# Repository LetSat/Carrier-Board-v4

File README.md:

# Carrier_Board_V3
2019 Spring semester started, updated design, carrier board using the TX2i not TK1

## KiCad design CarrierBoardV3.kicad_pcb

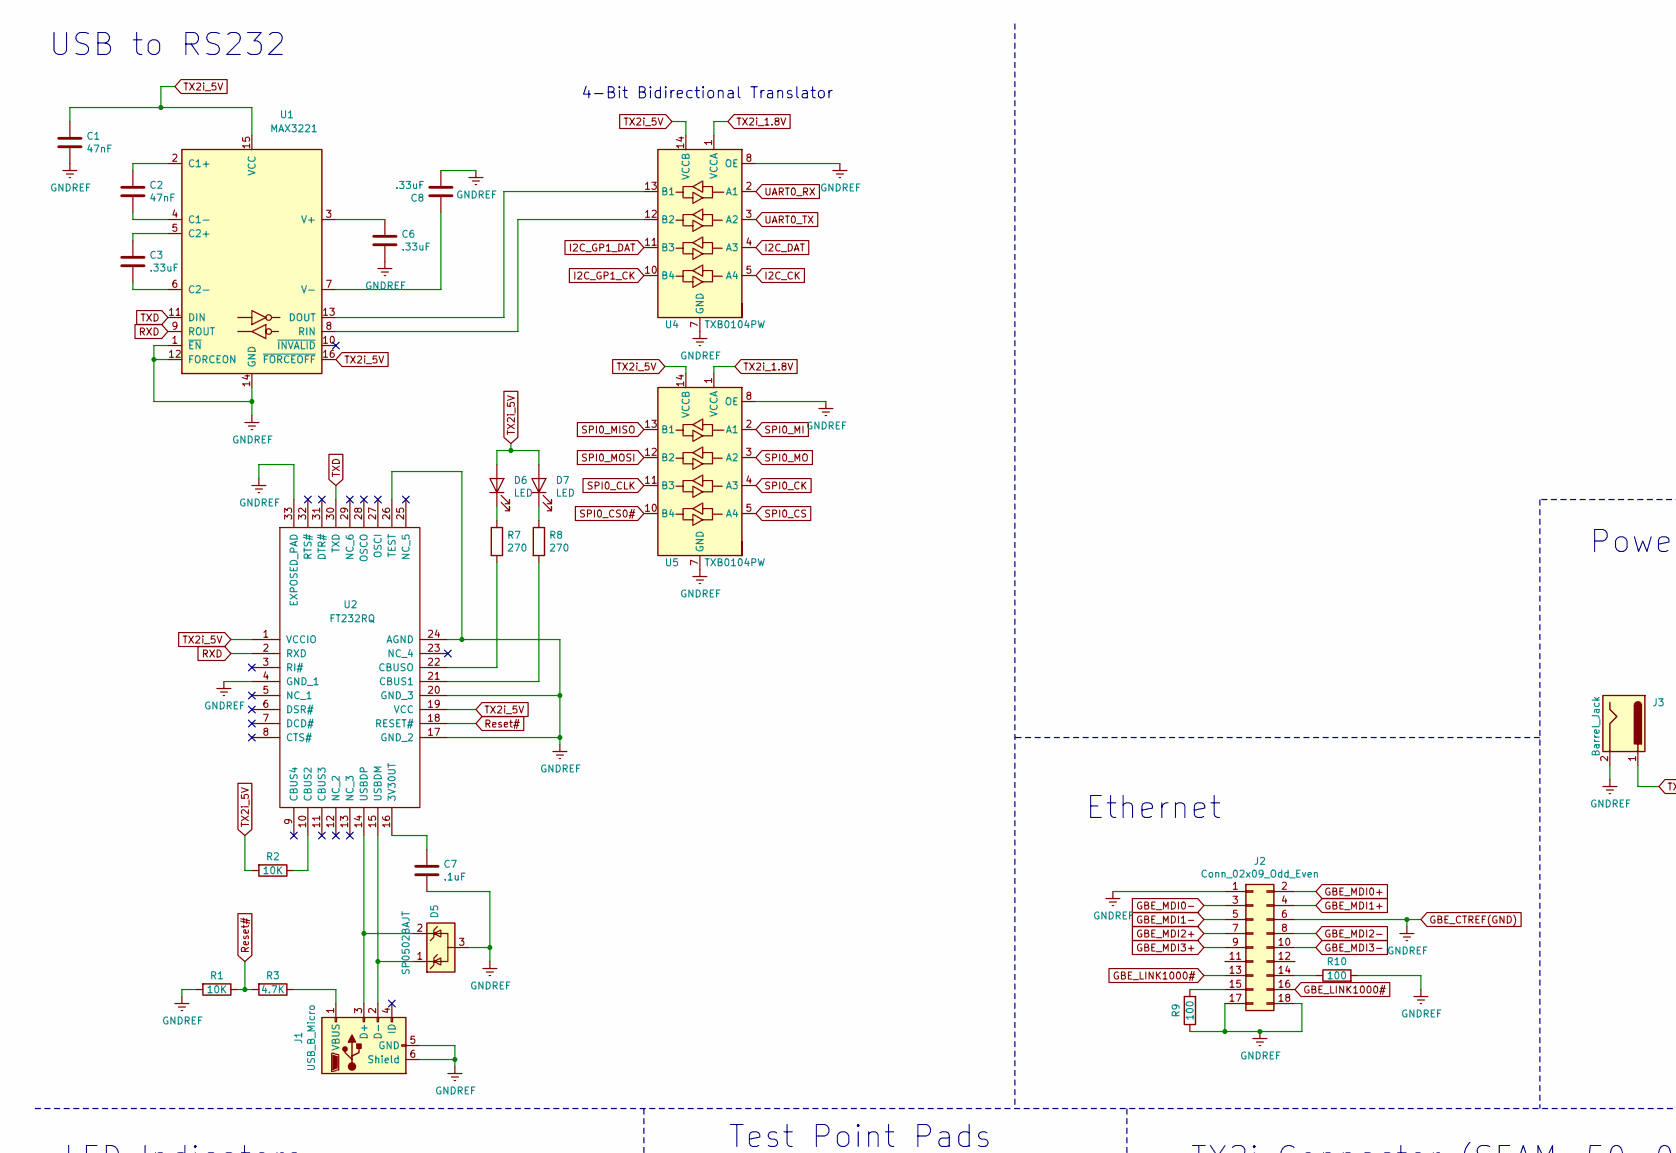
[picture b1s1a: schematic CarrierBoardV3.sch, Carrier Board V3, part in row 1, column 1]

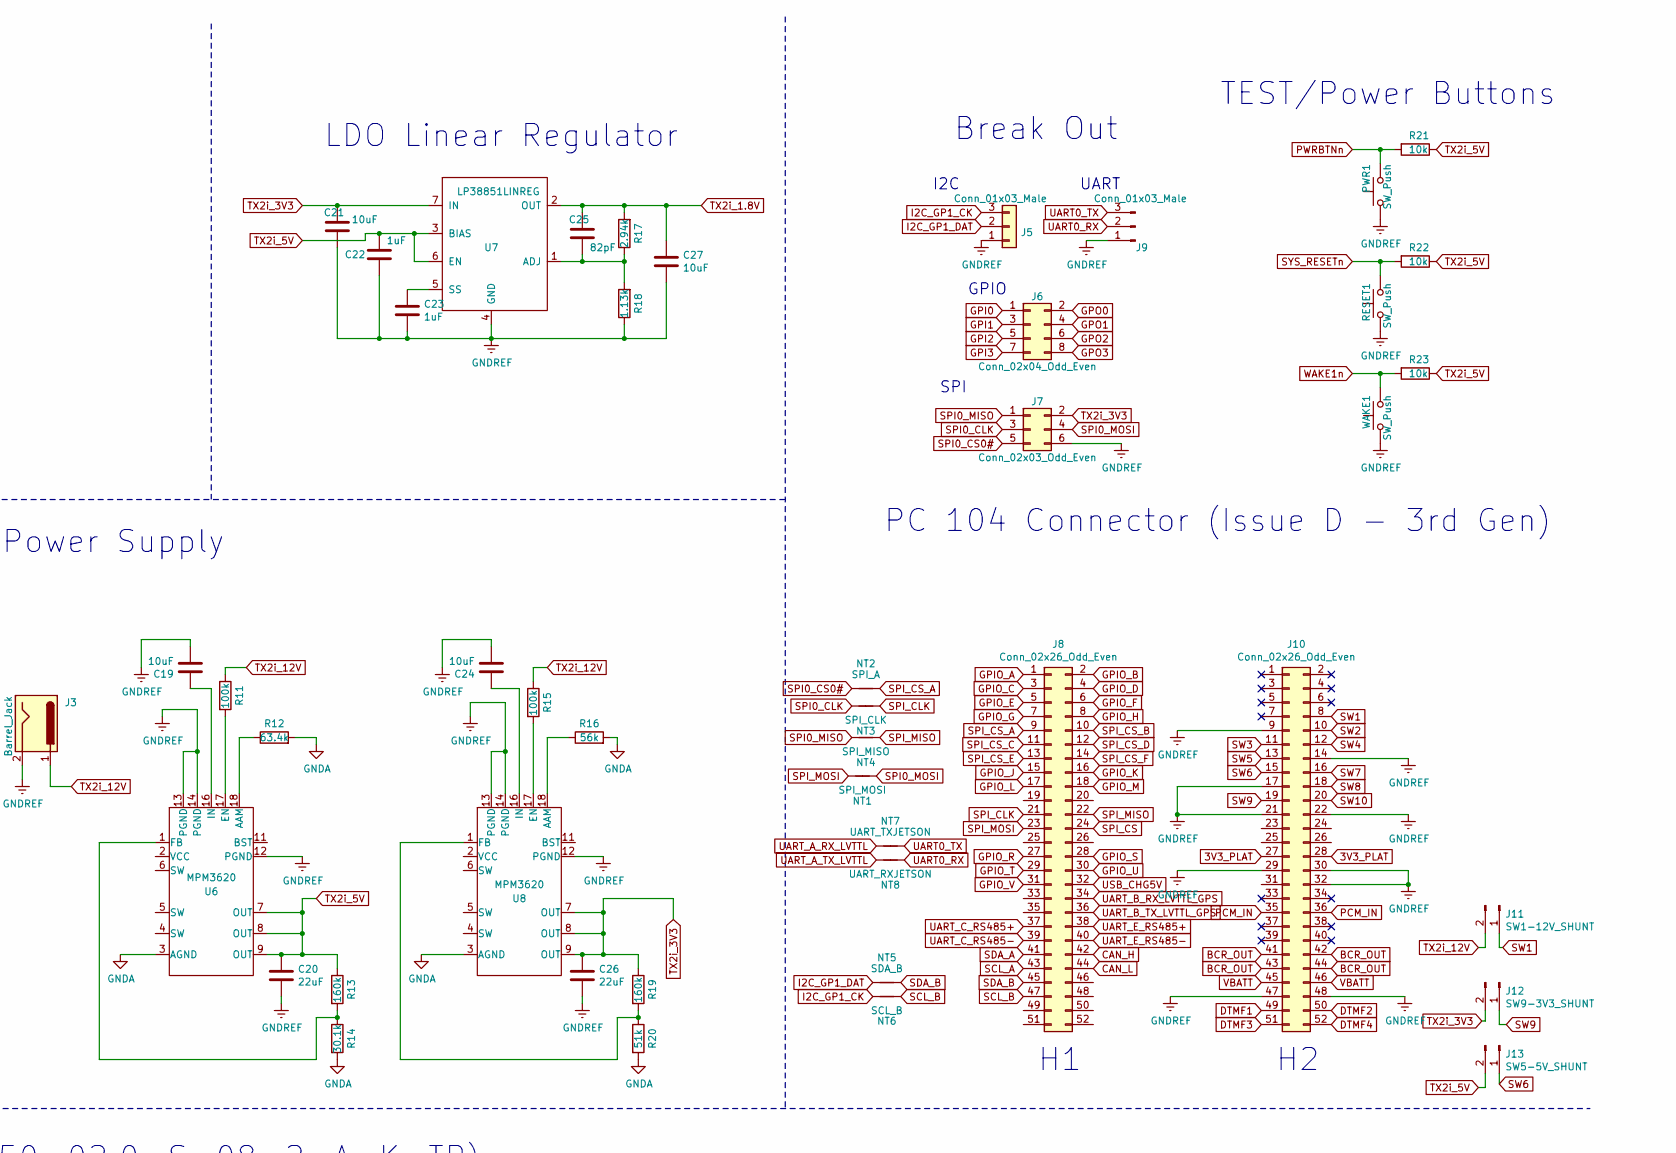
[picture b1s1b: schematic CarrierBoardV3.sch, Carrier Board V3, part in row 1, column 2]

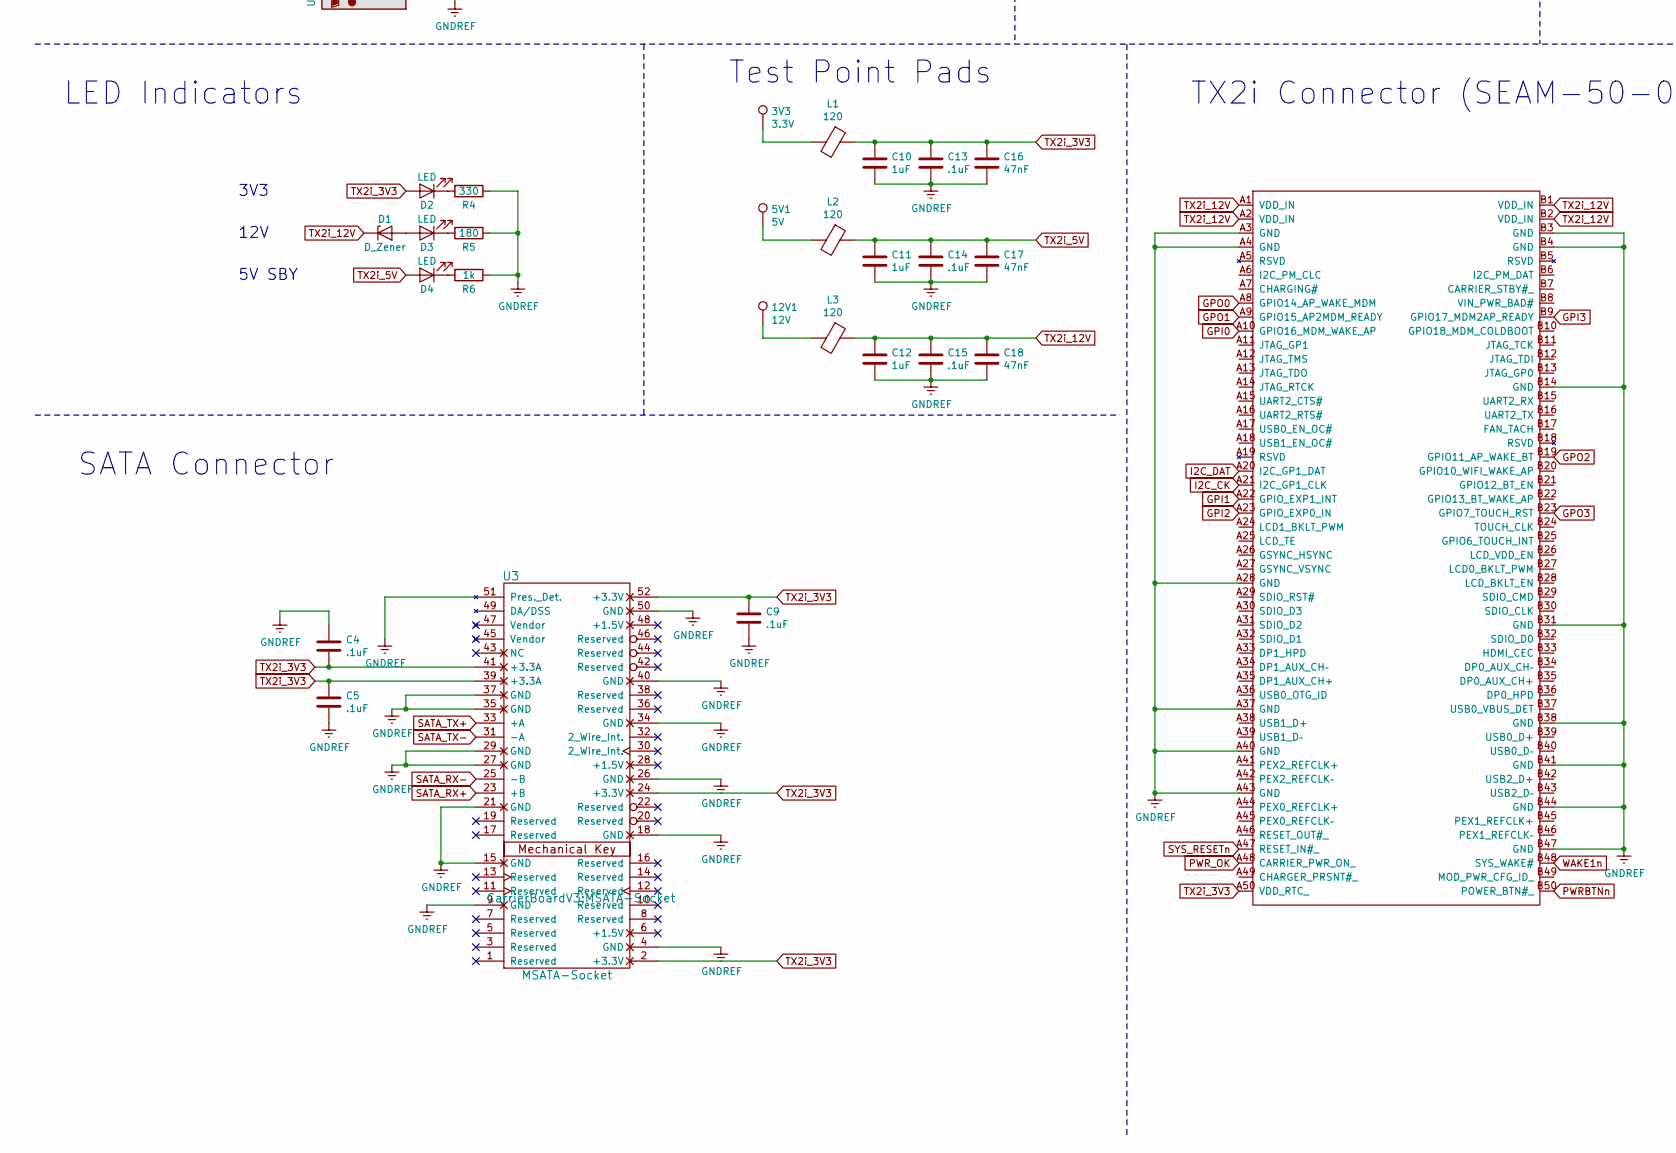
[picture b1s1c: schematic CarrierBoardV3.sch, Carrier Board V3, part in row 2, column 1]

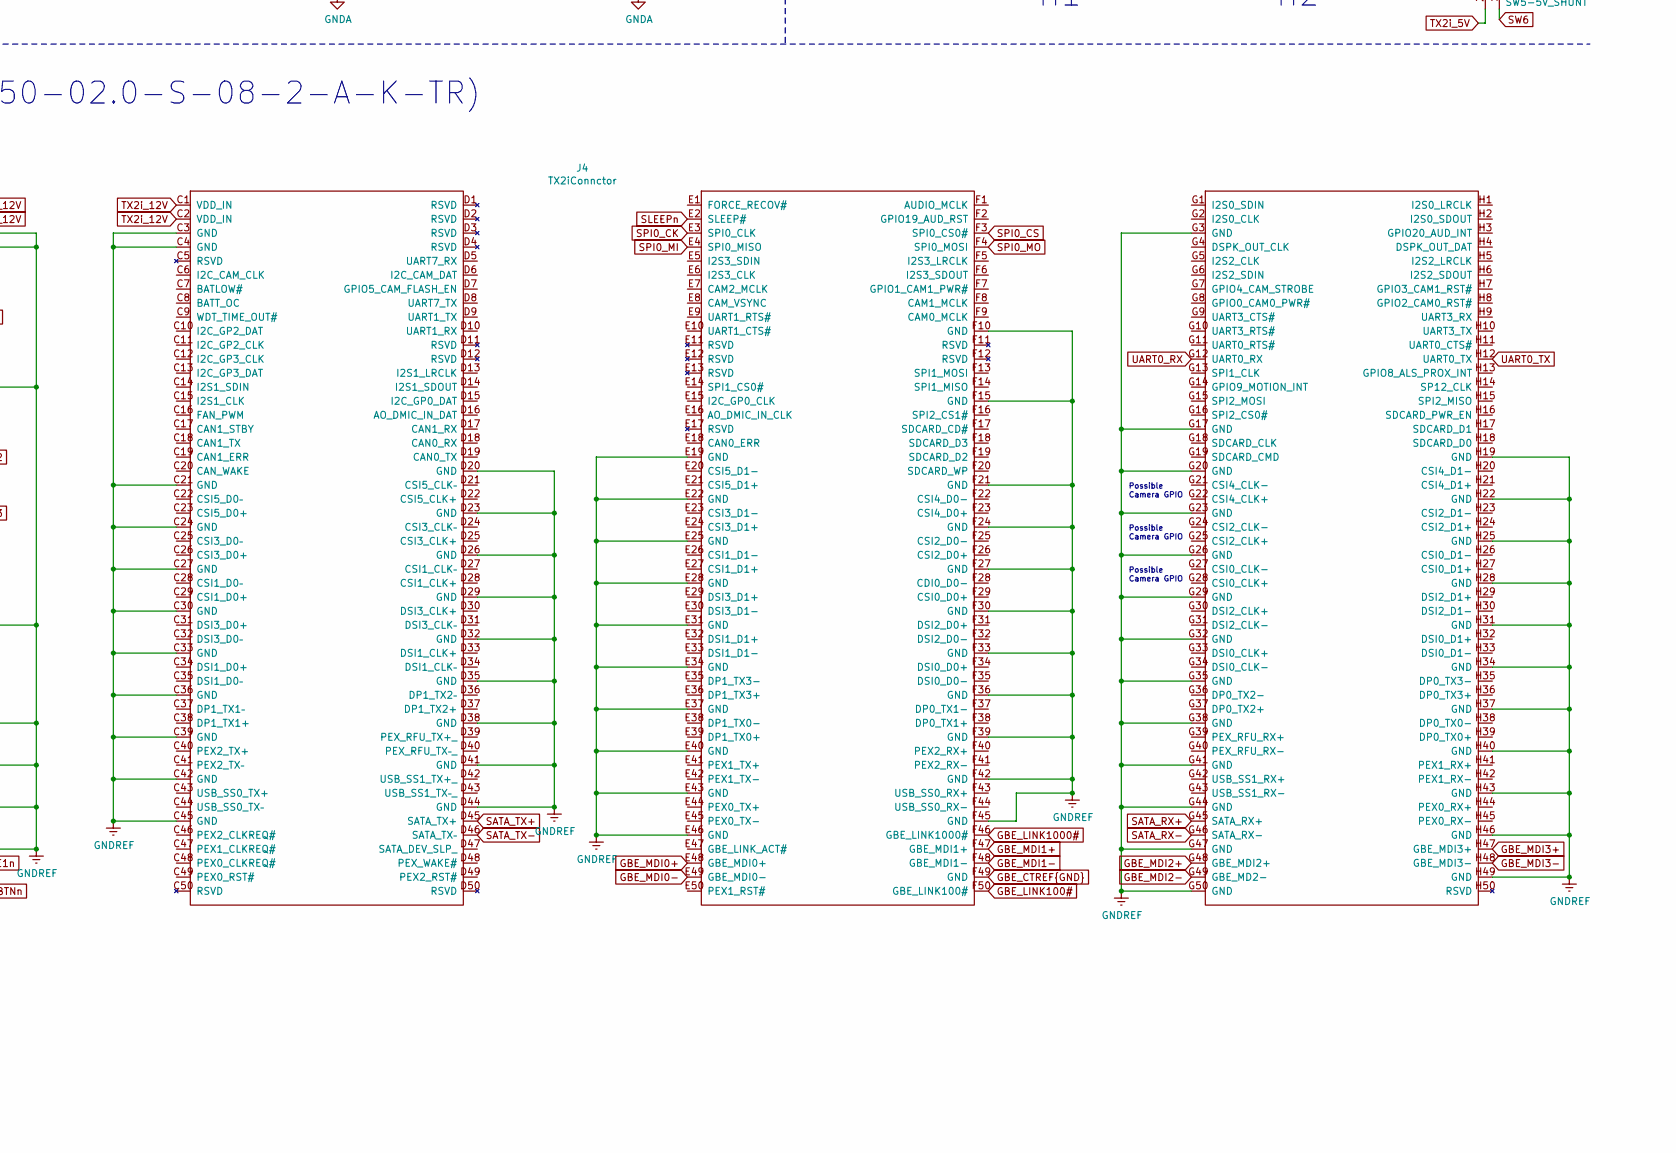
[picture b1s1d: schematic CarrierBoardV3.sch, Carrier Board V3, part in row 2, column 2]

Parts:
3V3: 3.3V; TestPoint_Pad_4.0x4.0mm
5V1: 5V; TestPoint_Pad_4.0x4.0mm
12V1: 12V; TestPoint_Pad_4.0x4.0mm
C1, C2, C16, C17, C18: 47nF; C_0603_1608Metric
C3, C6, C8: .33uF; C_0603_1608Metric
C4, C5, C7, C9, C13, C14, C15: .1uF; C_0603_1608Metric
C10, C11, C12, C22, C23: 1uF; C_0603_1608Metric
C19, C21, C24, C27: 10uF; C_0603_1608Metric
C20, C26: 22uF; C_0603_1608Metric
C25: 82pF; C_0603_1608Metric
D1: D_Zener; LED_0603_1608Metric
D2, D3, D4, D6, D7: LED; LED_0603_1608Metric
D5: SP0502BAJT; SOT-323_SC-70
J1: USB_B_Micro; USB_Micro-B_Molex-105017-0001
J2: Conn_02x09_Odd_Even; Ethernet
J3: Barrel_Jack; BarrelJack_CUI_PJ-036AH-SMT_Horizontal
J4: TX2iConnctor; SEAM-50-02.0-XX-08-X-A
J5, J9: Conn_01x03_Male; PinHeader_1x03_P2.54mm_Vertical
J6: Conn_02x04_Odd_Even; PinHeader_2x04_P2.54mm_Vertical
J7: Conn_02x03_Odd_Even; PinHeader_2x03_P2.54mm_Vertical
J8, J10: Conn_02x26_Odd_Even; ESQ-126-XX-X-D
J11: SW1-12V_SHUNT; SolderJumper-2_P1.3mm_Open_Pad1.0x1.5mm
J12: SW9-3V3_SHUNT; SolderJumper-2_P1.3mm_Open_Pad1.0x1.5mm
J13: SW5-5V_SHUNT; SolderJumper-2_P1.3mm_Open_Pad1.0x1.5mm
L1, L2, L3: 120; R_0603_1608Metric
NT1: SPI_MOSI; NetTie-2_SMD_Pad0.5mm
NT2: SPI_A; NetTie-2_SMD_Pad0.5mm
NT3: SPI_CLK; NetTie-2_SMD_Pad0.5mm
NT4: SPI_MISO; NetTie-2_SMD_Pad0.5mm
NT5: SDA_B; NetTie-2_SMD_Pad0.5mm
NT6: SCL_B; NetTie-2_SMD_Pad0.5mm
NT7: UART_TXJETSON; NetTie-2_SMD_Pad0.5mm
NT8: UART_RXJETSON; NetTie-2_SMD_Pad0.5mm
PWR1: SW_Push; SW_SPST_B3U-1000P
R1, R2: 10K; R_0603_1608Metric
R3: 4.7K; R_0603_1608Metric
R4: 330; R_0603_1608Metric
R5: 180; R_0603_1608Metric
R6: 1k; R_0603_1608Metric
R7, R8: 270; R_0603_1608Metric
R9, R10: 100; R_0603_1608Metric
R11, R15: 100k; R_0603_1608Metric
R12: 63.4k; R_0603_1608Metric
R13, R19: 160k; R_0603_1608Metric
R14: 30.1k; R_0603_1608Metric
R16: 56k; R_0603_1608Metric
R17: 2.94k; R_0603_1608Metric
R18: 1.13k; R_0603_1608Metric
R20: 51k; R_0603_1608Metric
R21, R22, R23: 10k; R_0603_1608Metric
RESET1: SW_Push; SW_SPST_B3U-1000P
U1: MAX3221; TSSOP-16_4.4x5mm_P0.65mm
U2: FT232RQ; QFN-32-1EP_5x5mm_P0.5mm_EP3.1x3.1mm
U3: MSATA-Socket
U4, U5: TXB0104PW; TSSOP-14_4.4x5mm_P0.65mm
U6, U8: MPM3620; QFN-20
U7: LP38851LINREG; SOIC-8-1EP_3.9x4.9mm_P1.27mm_EP2.35x2.35mm
WAKE1: SW_Push; SW_SPST_B3U-1000P

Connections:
3V3_PLAT: J10.27, J10.28
BCR_OUT: J10.41, J10.42, J10.43, J10.44
CAN_H: J8.42
CAN_L: J8.44
DTMF1: J10.49
DTMF2: J10.50
DTMF3: J10.51
DTMF4: J10.52
GBE_CTREF(GND): C1.2, C4.2, C5.2, C6.2, C7.2, C8.2, C9.2, C10.2, C11.2, C12.2, C13.2, C14.2, C15.2, C16.2, C17.2, C18.2, C19.2, C20.2, C21.2, C22.2, C23.2, C24.2, C26.2, C27.2, D5.3 (A), J1.5 (GND), J1.6 (Shield), J2.1, J2.6, J2.17, J2.18, J3.2, J3.3, J4.A3 (GND), J4.A4 (GND), J4.A28 (GND), J4.A37 (GND), J4.A40 (GND), J4.A43 (GND), J4.B3 (GND), J4.B4 (GND), J4.B14 (GND), J4.B31 (GND), J4.B38 (GND), J4.B41 (GND), J4.B44 (GND), J4.B47 (GND), J4.C3 (GND), J4.C4 (GND), J4.C21 (GND), J4.C24 (GND), J4.C27 (GND), J4.C30 (GND), J4.C33 (GND), J4.C36 (GND), J4.C39 (GND), J4.C42 (GND), J4.C45 (GND), J4.D20 (GND), J4.D23 (GND), J4.D26 (GND), J4.D29 (GND), J4.D32 (GND), J4.D35 (GND), J4.D38 (GND), J4.D41 (GND), J4.D44 (GND), J4.E19 (GND), J4.E22 (GND), J4.E25 (GND), J4.E28 (GND), J4.E31 (GND), J4.E34 (GND), J4.E37 (GND), J4.E40 (GND), J4.E43 (GND), J4.E46 (GND), J4.F10 (GND), J4.F15 (GND), J4.F21 (GND), J4.F24 (GND), J4.F27 (GND), J4.F30 (GND), J4.F33 (GND), J4.F36 (GND), J4.F39 (GND), J4.F42 (GND), J4.F45 (GND), J4.G3 (GND), J4.G17 (GND), J4.G20 (GND), J4.G23 (GND), J4.G26 (GND), J4.G29 (GND), J4.G32 (GND), J4.G35 (GND), J4.G38 (GND), J4.G41 (GND), J4.G44 (GND), J4.G47 (GND), J4.G50 (GND), J4.H19 (GND), J4.H22 (GND), J4.H25 (GND), J4.H28 (GND), J4.H31 (GND), J4.H34 (GND), J4.H37 (GND), J4.H40 (GND), J4.H43 (GND), J4.H46 (GND), J4.H49 (GND), J5.1, J7.6, J9.1, J10.9, J10.14, J10.17, J10.21, J10.22, J10.29, J10.30, J10.32, J10.47, J10.48, PWR1.1, R1.2, R4.1, R5.1, R6.1, R9.1, R10.2, R18.1, RESET1.1, U1.1 (~EN), U1.12 (FORCEON), U1.14 (GND), U2.4 (GND_1), U2.17 (GND_2), U2.20 (GND_3), U2.24 (AGND), U2.26 (TEST), U2.33 (EXPOSED_PAD), U3.4 (GND), U3.9 (GND), U3.15 (GND), U3.18 (GND), U3.21 (GND), U3.26 (GND), U3.27 (GND), U3.29 (GND), U3.34 (GND), U3.35 (GND), U3.37 (GND), U3.40 (GND), U3.50 (GND), U3.51 (Pres._Det.), U4.7 (GND), U4.8 (OE), U5.7 (GND), U5.8 (OE), U6.12 (PGND), U6.13 (PGND), U6.14 (PGND), U7.4 (GND), U8.12 (PGND), U8.13 (PGND), U8.14 (PGND), WAKE1.1; also elsewhere on the board
GBE_CTREF{GND}: J4.F49 (GND)
GBE_LINK100#: J4.F50 (GBE_LINK100#)
GBE_LINK1000#: J2.13, J2.16, J4.F46 (GBE_LINK1000#)
GBE_MDI0+: J2.2, J4.E48 (GBE_MDI0+)
GBE_MDI0-: J2.3, J4.E49 (GBE_MDI0-)
GBE_MDI1+: J2.4, J4.F47 (GBE_MDI1+)
GBE_MDI1-: J2.5, J4.F48 (GBE_MDI1-)
GBE_MDI2+: J2.7, J4.G48 (GBE_MDI2+)
GBE_MDI2-: J2.8, J4.G49 (GBE_MD2-)
GBE_MDI3+: J2.9, J4.H47 (GBE_MDI3+)
GBE_MDI3-: J2.10, J4.H48 (GBE_MDI3-)
GNDA: R12.2, R14.2, R16.2, R20.2, U6.3 (AGND), U8.3 (AGND)
GPI0: J4.A10 (GPIO16_MDM_WAKE_AP), J6.1
GPI1: J4.A22 (GPIO_EXP1_INT), J6.3
GPI2: J4.A23 (GPIO_EXP0_IN), J6.5
GPI3: J4.B9 (GPIO17_MDM2AP_READY), J6.7
GPIO_A: J8.1
GPIO_B: J8.2
GPIO_C: J8.3
GPIO_D: J8.4
GPIO_E: J8.5
GPIO_F: J8.6
GPIO_G: J8.7
GPIO_H: J8.8
GPIO_J: J8.15
GPIO_K: J8.16
GPIO_L: J8.17
GPIO_M: J8.18
GPIO_R: J8.27
GPIO_S: J8.28
GPIO_T: J8.29
GPIO_U: J8.30
GPIO_V: J8.31
GPO0: J4.A8 (GPIO14_AP_WAKE_MDM), J6.2
GPO1: J4.A9 (GPIO15_AP2MDM_READY), J6.4
GPO2: J4.B19 (GPIO11_AP_WAKE_BT), J6.6
GPO3: J4.B23 (GPIO7_TOUCH_RST), J6.8
I2C_CK: J4.A21 (I2C_GP1_CLK), U4.5 (A4)
I2C_DAT: J4.A20 (I2C_GP1_DAT), U4.4 (A3)
I2C_GP1_CK: J5.3, NT6.1, U4.10 (B4)
I2C_GP1_DAT: J5.2, NT5.1, U4.11 (B3)
unnamed: 3V3.1, L1.2
unnamed 51: 5V1.1, L2.2; also elsewhere on the board
unnamed 52: 12V1.1, L3.2; also elsewhere on the board
unnamed: C2.1, U1.2 (C1+)
unnamed: C2.2, U1.4 (C1-)
unnamed: C3.1, U1.5 (C2+)
unnamed: C3.2, U1.6 (C2-)
unnamed: C6.1, U1.3 (V+)
unnamed: C7.1, U2.16 (3V30UT)
unnamed: C8.1, U1.7 (V-)
unnamed: C19.1, U6.16 (IN)
unnamed: C23.1, U7.5 (SS)
unnamed: C24.1, U8.16 (IN)
unnamed: C25.2, R17.1, R18.2, U7.1 (ADJ)
unnamed: D1.2 (A), D3.2 (A)
unnamed: D2.1 (K), R4.2
unnamed: D3.1 (K), R5.2
unnamed: D4.1 (K), R6.2
unnamed: D5.1 (K), J1.2 (D-), U2.15 (USBDM)
unnamed: D5.2 (K), J1.3 (D+), U2.14 (USBDP)
unnamed: D6.1 (K), R7.1
unnamed: D7.1 (K), R8.1
unnamed: J1.1 (VBUS), R3.1
unnamed: J2.14, R10.1
unnamed: J2.15, R9.2
unnamed: R2.1, U2.10 (CBUS2)
unnamed: R7.2, U2.22 (CBUSO)
unnamed: R8.2, U2.21 (CBUS1)
unnamed: R11.2, U6.17 (EN)
unnamed: R12.1, U6.18 (AAM)
unnamed: R13.2, R14.1, U6.1 (FB)
unnamed: R15.2, U8.17 (EN)
unnamed: R16.1, U8.18 (AAM)
unnamed: R19.2, R20.1, U8.1 (FB)
unnamed: U1.8 (RIN), U4.12 (B2)
unnamed: U1.13 (DOUT), U4.13 (B1)
PCM_IN: J10.35, J10.36
PWRBTNn: J4.B50 (POWER_BTN#_), PWR1.2, R21.2; also elsewhere on the board
PWR_OK: J4.A48 (CARRIER_PWR_ON_)
RXD: U1.9 (ROUT), U2.2 (RXD)
Reset#: R1.1, R3.2, U2.18 (RESET#)
SATA_RX+: J4.G45 (SATA_RX+), U3.23 (+B)
SATA_RX-: J4.G46 (SATA_RX-), U3.25 (-B)
SATA_TX+: J4.D45 (SATA_TX+), U3.33 (+A)
SATA_TX-: J4.D46 (SATA_TX–), U3.31 (-A)
SCL_A: J8.43
SCL_B: J8.47, NT6.2
SDA_A: J8.41
SDA_B: J8.45, NT5.2
SLEEPn: J4.E2 (SLEEP#)
SPI0_CK: J4.E3 (SPI0_CLK), U5.4 (A3)
SPI0_CLK: J7.3, NT3.1, U5.11 (B3)
SPI0_CS: J4.F3 (SPI0_CS0#), U5.5 (A4)
SPI0_CS0#: J7.5, NT2.1, U5.10 (B4)
SPI0_MI: J4.E4 (SPI0_MISO), U5.2 (A1)
SPI0_MISO: J7.1, NT4.1, U5.13 (B1)
SPI0_MO: J4.F4 (SPI0_MOSI), U5.3 (A2)
SPI0_MOSI: J7.4, NT1.2, U5.12 (B2)
SPI_CLK: J8.21, NT3.2
SPI_CS: J8.24
SPI_CS_A: J8.9, NT2.2
SPI_CS_B: J8.10
SPI_CS_C: J8.11
SPI_CS_D: J8.12
SPI_CS_E: J8.13
SPI_CS_F: J8.14
SPI_MISO: J8.22, NT4.2
SPI_MOSI: J8.23, NT1.1
SW1: J10.8, J11.1
SW2: J10.10
SW3: J10.11
SW4: J10.12
SW5: J10.13
SW6: J10.15, J13.1
SW7: J10.16
SW8: J10.18
SW9: J10.19, J12.1
SW10: J10.20
SYS_RESETn: J4.A47 (RESET_IN#_), R22.2, RESET1.2; also elsewhere on the board
TX2i_1.8V: C25.1, C27.1, R17.2, U4.1 (VCCA), U5.1 (VCCA), U7.2 (OUT)
TX2i_3V3: C4.1, C5.1, C9.1, C10.1, C13.1, C16.1, C21.1, C26.1, D2.2 (A), J4.A50 (VDD_RTC_), J7.2, J12.2, L1.1, R19.1, U3.2 (+3.3V), U3.24 (+3.3V), U3.39 (+3.3A), U3.41 (+3.3A), U3.52 (+3.3V), U7.7 (IN), U8.7 (OUT), U8.8 (OUT), U8.9 (OUT)
TX2i_5V: C1.1, C11.1, C14.1, C17.1, C20.1, C22.1, D4.2 (A), D6.2 (A), D7.2 (A), J13.2, L2.1, R2.2, R13.1, R21.1, R22.1, R23.1, U1.15 (VCC), U1.16 (~FORCEOFF), U2.1 (VCCIO), U2.19 (VCC), U4.14 (VCCB), U5.14 (VCCB), U6.7 (OUT), U6.8 (OUT), U6.9 (OUT), U7.3 (BIAS), U7.6 (EN)
TX2i_12V: C12.1, C15.1, C18.1, D1.1 (K), J3.1, J4.A1 (VDD_IN), J4.A2 (VDD_IN), J4.B1 (VDD_IN), J4.B2 (VDD_IN), J4.C1 (VDD_IN), J4.C2 (VDD_IN), J11.2, L3.1, R11.1, R15.1
TXD: U1.11 (DIN), U2.30 (TXD)
UART0_RX: J4.G12 (UART0_RX), J9.2, NT8.2, U4.2 (A1)
UART0_TX: J4.H12 (UART0_TX), J9.3, NT7.1, U4.3 (A2)
UART_A_RX_LVTTL: J8.33, NT7.2
UART_A_TX_LVTTL: J8.35, NT8.1
UART_B_RX_LVTTL_GPS: J8.34
UART_B_TX_LVTTL_GPS: J8.36
UART_C_RS485+: J8.37
UART_C_RS485-: J8.39
UART_E_RS485+: J8.38
UART_E_RS485-: J8.40
USB_CHG5V: J8.32
VBATT: J10.45, J10.46
WAKE1n: J4.B48 (SYS_WAKE#), R23.2, WAKE1.2; also elsewhere on the board

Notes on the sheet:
TX2i Connector (SEAM-50-02.0-S-08-2-A-K-TR)
PC 104 Connector (Issue D - 3rd Gen)
SATA Connector
I2C
UART
GPIO
SPI
Break Out
TEST/Power Buttons
3V3
12V
5V SBY
LED Indicators
USB to RS232
Ethernet
Test Point Pads
Power Supply
Possible Camera GPIO
4-Bit Bidirectional Translator
LDO Linear Regulator

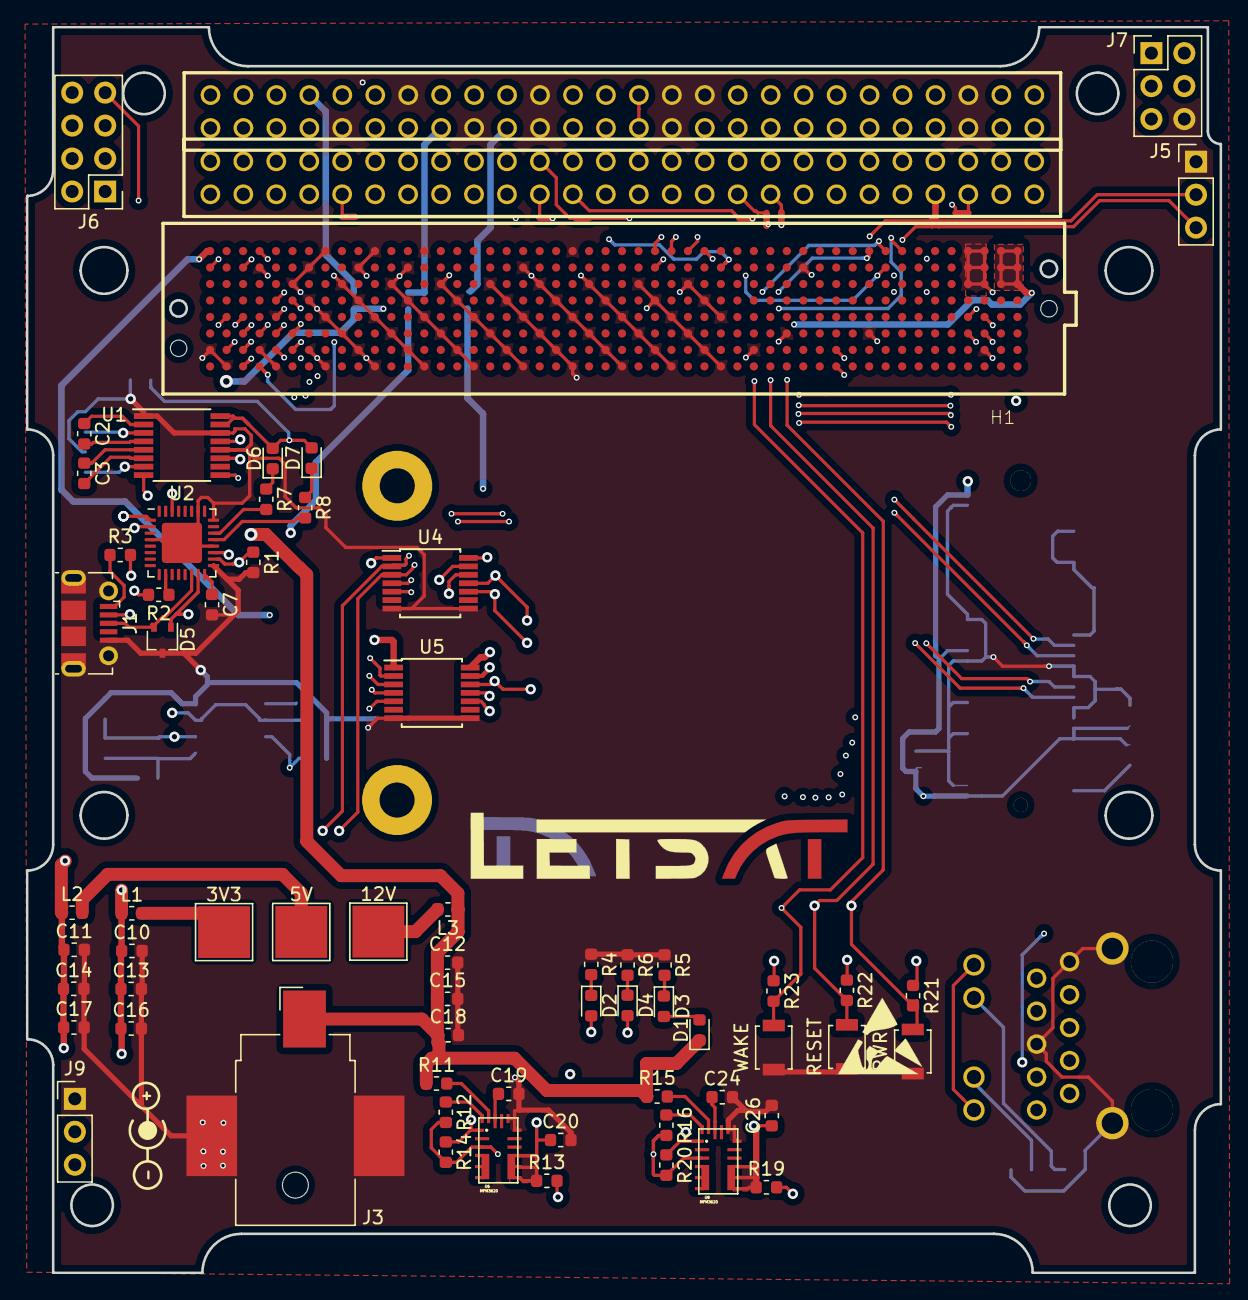
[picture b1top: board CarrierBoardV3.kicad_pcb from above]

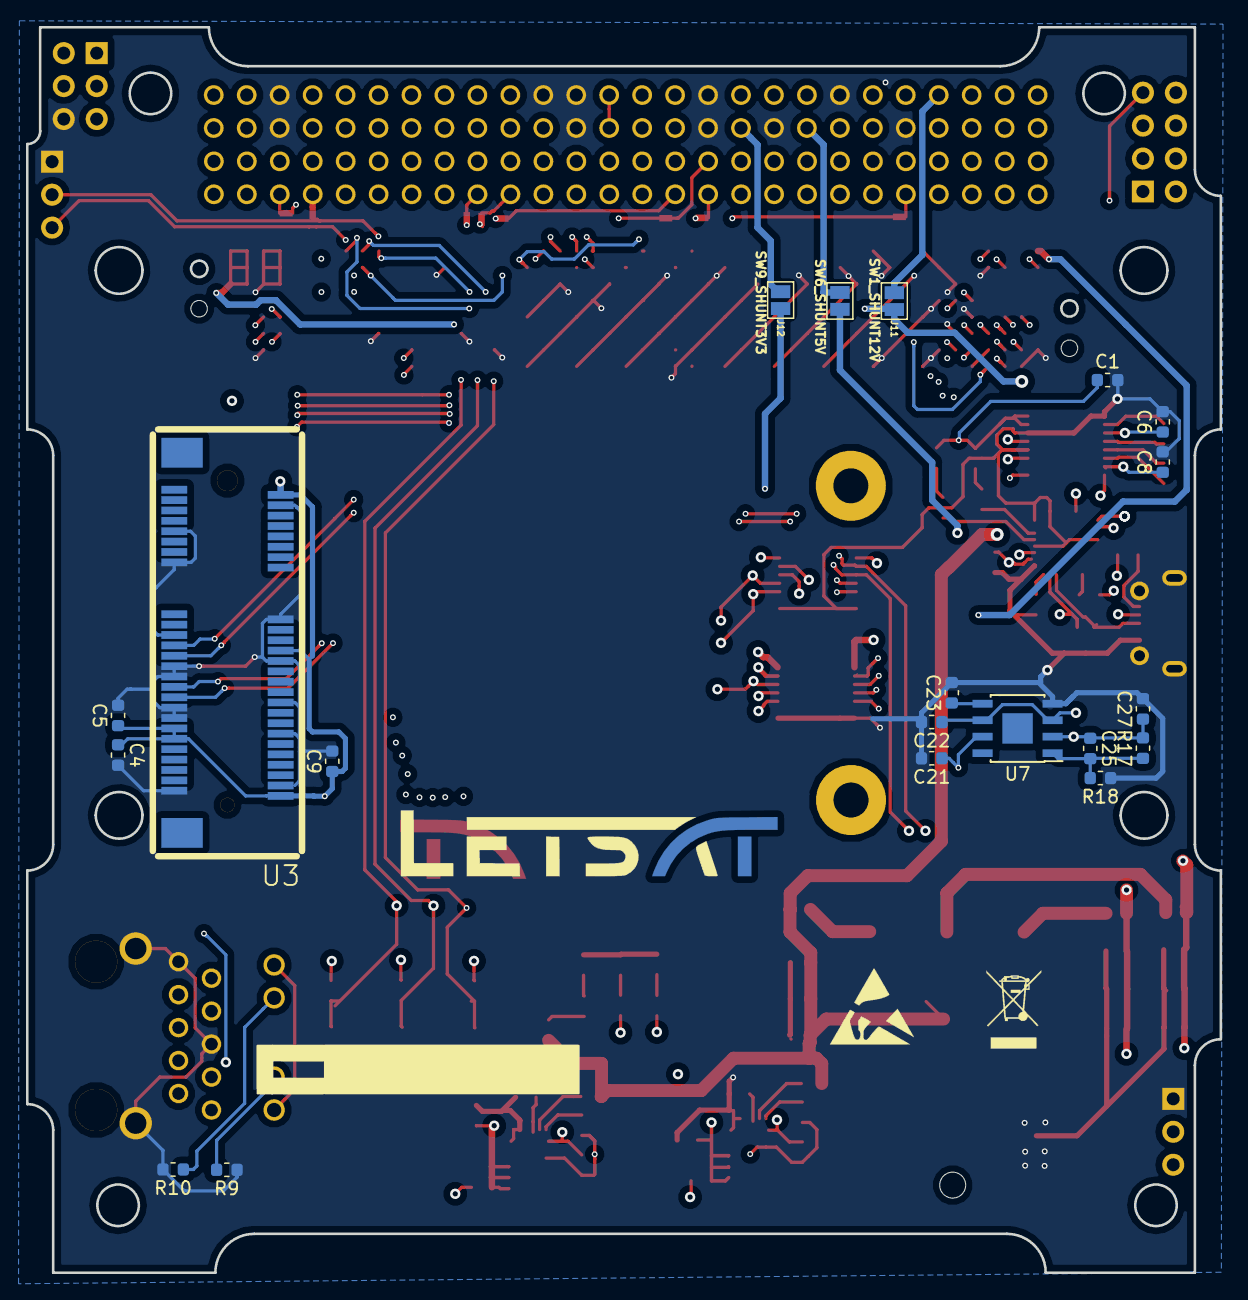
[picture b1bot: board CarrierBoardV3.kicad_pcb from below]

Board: 4 copper layers, 92.0 x 96.0 mm, 97 parts (20 on the bottom side), 98 nets.

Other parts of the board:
5V: 5V; TestPoint_Pad_4.0x4.0mm
12V: 12V; TestPoint_Pad_4.0x4.0mm
M1, M2: MountingHole_2.7mm_M2.5_Pad
PWR: SW_Push; SW_SPST_B3U-1000P
RESET: SW_Push; SW_SPST_B3U-1000P
WAKE: SW_Push; SW_SPST_B3U-1000P

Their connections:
GBE_CTREF(GND): PWR.1, RESET.1, WAKE.1; also elsewhere on the board
unnamed 51: 5V.1; also elsewhere on the board
unnamed 52: 12V.1; also elsewhere on the board
PWRBTNn: PWR.2; also elsewhere on the board
SYS_RESETn: RESET.2; also elsewhere on the board
WAKE1n: WAKE.2; also elsewhere on the board

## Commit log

2019-02-05 Fixed lib location
2019-02-05 Test
2019-02-07 Added pins E-H
2019-02-07 fixed
2019-02-09 TX2i Connector Edits (Flags Added)
2019-02-10 Edited the schematic
    Included the MSATA connector, have not finished it yet though.
2019-02-14 Add PC104 connector
2019-02-17 Schematic Update Minus Ethernet & USB to RS232
2019-02-17 Edited Schematic
2019-02-20 Assigned all footprints except TX2i connector
2019-02-20 Fixed errors in schematic numbering
2019-02-20 Added footprints for TX2i connector and PC-104 connector
2019-02-21 Fixed PC104 footprint
2019-02-21 added more footprints
2019-02-22 All components added with footprints
2019-02-22 All components added with footprints, done...
2019-02-24 Added some revisions form the schematic review 1
2019-02-25 More schematic revisions
2019-02-26 Added more schematic review 1 updates
2019-02-27 Finished updates from schematic review 1
2019-03-01 Second to last changes for revision 1
2019-03-11 Part of Layout complete
2019-03-11 PCB Layout almost done, gnd fills and PC104 update needed
2019-03-11 Added LetSat Logo
2019-03-13 Layout revisions
2019-03-13 Layout clean ups and revisions
2019-03-14 Layout revisions for signal and power lines
2019-03-16 ethernet trace matches finished
2019-03-16 done with all trace revisions, need to add sata connector holes and verify with prabodh on a DRC problem, all routes are connected
2019-03-16 Sata mounting holes added, all routes connected and finished as far as I know, waiting for Prabodh to have a final look over
2019-03-16 All trace edits complete and re routes
2019-03-17 PCB touch up
    Added shunts for SWs and fixed some trace shorts
2019-03-18 fixed stuff
2019-03-18 zipped gerber
2019-03-23 finished schematic update for OBC and Tranciever
2019-03-24 Routed all new edits done to PC104
2019-03-24 Finished Ready for FAB
    S/N:0C137_V3_SP19
2019-03-24 minor changes
2019-04-05 Fixed TX2i connector orientation, all traces done, trace matching needs to be done still
2019-04-05 traces complete, need help length matching becasue I can not seem to get it, no idea why???
2019-04-06 Finished Rev 3 with correct orientation of TX2i connector
2019-04-12 Voltage regulator trace fix
